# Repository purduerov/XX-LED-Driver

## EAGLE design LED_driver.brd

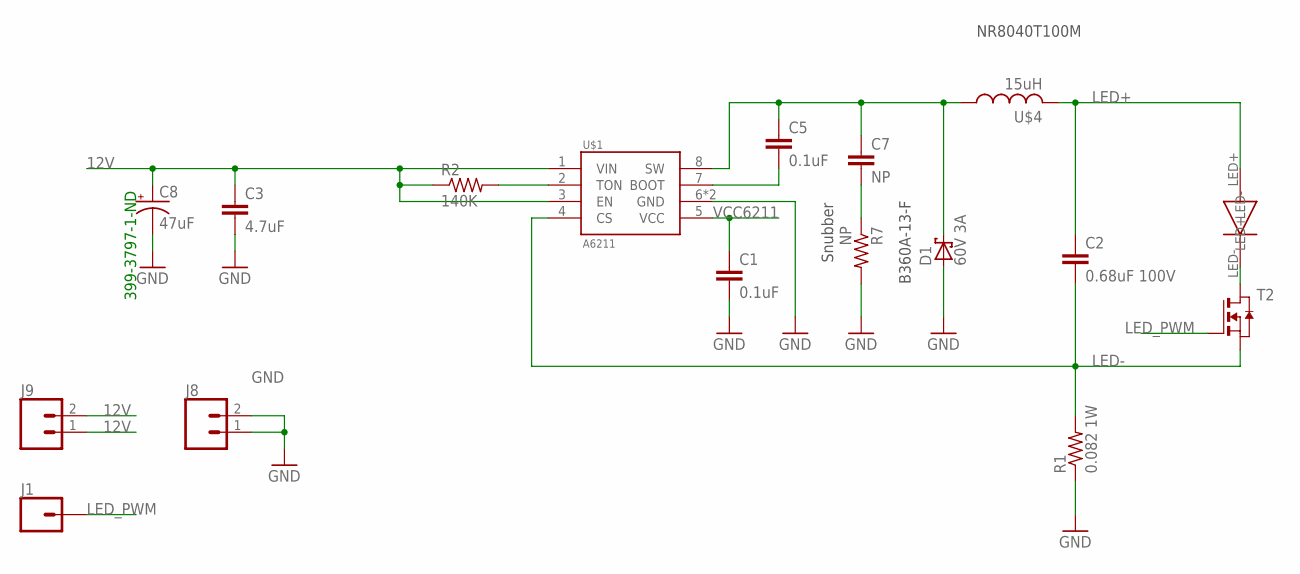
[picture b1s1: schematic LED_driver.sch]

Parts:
C1, C5: 0.1uF; C0603
C2: 0.68uF 100V; C0805
C3: 4.7uF; C0603
C7: NP; C0603
C8: 47uF; CTAN(7.30_4.30MM)
D1: 60V 3A; SMA
J1: CONN_01; 1X01
J8, J9: CONN_021X02_NO_SILK; 1X02_NO_SILK
R1: 0.082 1W; R2512
R2: 140K; R0603
R7: NP; R1206
T2: NMOSSOT23; SOT-23
U$1: A6211; SOIC8N-LJ
U$3: LED_00H53
U$4: 15uH; HCMA1305

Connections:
12V: C3.1, C8.+, J9.1, J9.2, R2.1, U$1.1 (VIN), U$1.3 (EN)
GND: C1.2, C3.2, C8.-, D1.A, J8.1, J8.2, R1.1, R7.2, U$1.6 (GND), U$1.PAD (GND)
LED+: C2.1, U$3.LED+, U$4.P$2 (2)
LED-: C2.2, R1.2, T2.2 (S), U$1.4 (CS)
LED_PWM: J1.1, T2.3 (G)
unnamed: R2.2, U$1.2 (TON)
unnamed: C7.2, R7.1
unnamed: T2.1 (D), U$3.LED-
unnamed: C5.2, U$1.7 (BOOT)
unnamed: C5.1, C7.1, D1.C, U$1.8 (SW), U$4.P$1 (1)
VCC6211: C1.1, U$1.5 (VCC)

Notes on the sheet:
NR8040T100M
B360A-13-F
Snubber
399-3797-1-ND

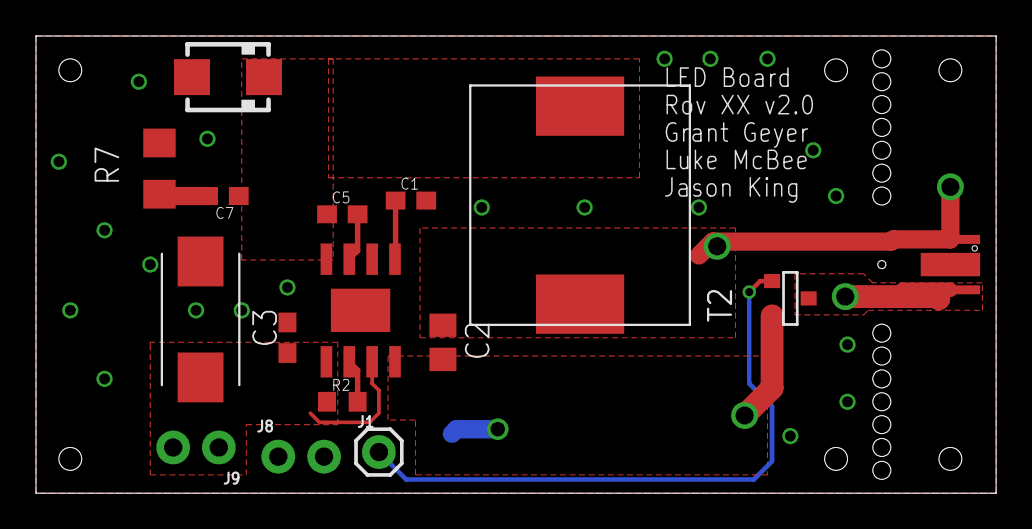
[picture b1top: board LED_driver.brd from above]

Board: 2 copper layers, 53.3 x 25.4 mm, 17 parts (1 on the bottom side), 11 nets.

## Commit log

2017-10-15 Added gitignore
2017-10-21 Initial push for LED Driver Board
2017-10-21 Almost done with version 1 of the LED Driver Board
2017-12-22 Grant's design with the cheaper LED placed on the board
2017-12-23 Changed layout so LED is on the end of the board. Fixed traces
2018-01-03 Made several improvements and allowed for the LED to be wired with through holes
2018-01-07 Added silkscreen
2018-01-07 Finishing up routing
2018-01-09 Added more drill holes
2018-02-24 added nmos and connected EN to 12V
2018-02-24 moved mosfet so end can still be broken off

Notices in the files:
parts and their libraries:
SparkFun-Connectors: Licensing: Creative Commons ShareAlike 4.0 International - https://creativecommons.org/licenses/by-sa/4.0
